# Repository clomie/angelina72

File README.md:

# Angelina72

72/68/64 keys irregular row staggered split keyboard.

## Layout and Default Keymap

# Photos

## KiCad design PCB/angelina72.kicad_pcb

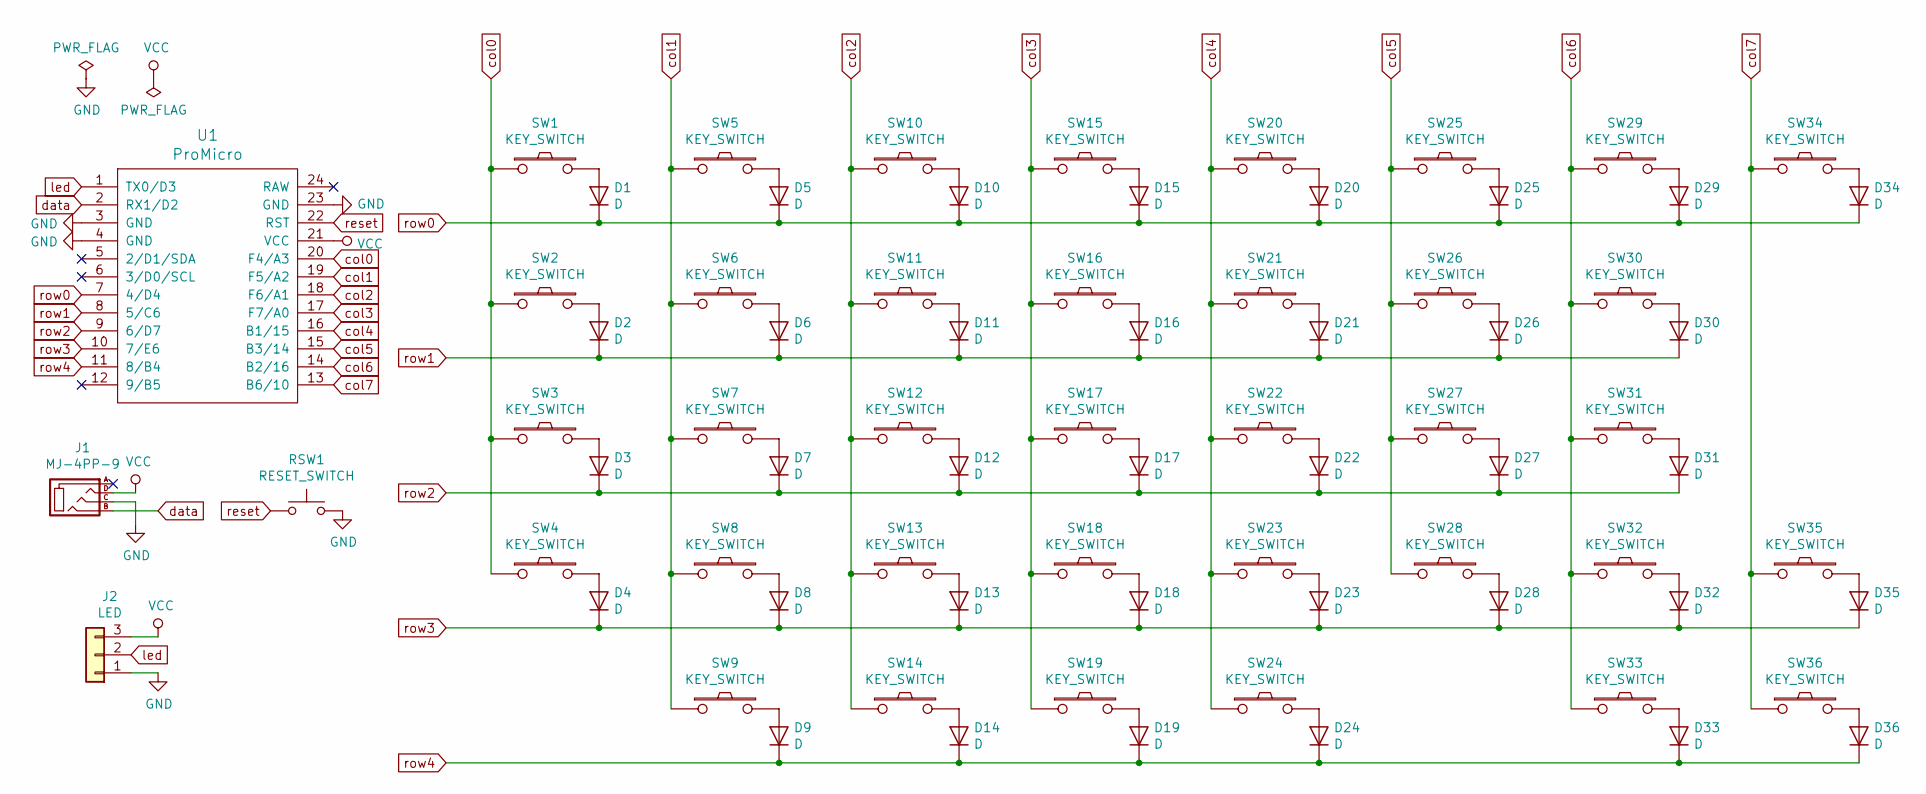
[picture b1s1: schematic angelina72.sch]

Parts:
D1, D2, D3, D4, D5, D6, D7, D8, D9, D10, D11, D12, D13, D14, D15, D16, D17, D18, D19, D20, D21, D22, D23, D24, D25, D26, D27, D28, D29, D30, D31, D32, D33, D34, D35, D36: D; D3_SMD
J1: MJ-4PP-9
J2: LED; StripLED_PAD
RSW1: RESET_SWITCH; ResetSW
SW1, SW2, SW3, SW4, SW5, SW6, SW7, SW8, SW10, SW11, SW12, SW13, SW14, SW15, SW16, SW17, SW18, SW20, SW21, SW22, SW23, SW25, SW26, SW27, SW28, SW29, SW30, SW31, SW32, SW33, SW34, SW35, SW36: KEY_SWITCH; CherryMX_Hotswap_1u
SW9, SW19, SW24: KEY_SWITCH; CherryMX_Hotswap_1.25u
U1: ProMicro

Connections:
GND: J1.C, J2.1, RSW1.2, U1.3 (GND), U1.4 (GND), U1.23 (GND)
unnamed: D1.2 (A), SW1.2
unnamed: D2.2 (A), SW2.2
unnamed: D3.2 (A), SW3.2
unnamed: D4.2 (A), SW4.2
unnamed: D5.2 (A), SW5.2
unnamed: D6.2 (A), SW6.2
unnamed: D7.2 (A), SW7.2
unnamed: D8.2 (A), SW8.2
unnamed: D9.2 (A), SW9.2
unnamed: D10.2 (A), SW10.2
unnamed: D11.2 (A), SW11.2
unnamed: D12.2 (A), SW12.2
unnamed: D13.2 (A), SW13.2
unnamed: D14.2 (A), SW14.2
unnamed: D15.2 (A), SW15.2
unnamed: D16.2 (A), SW16.2
unnamed: D17.2 (A), SW17.2
unnamed: D18.2 (A), SW18.2
unnamed: D19.2 (A), SW19.2
unnamed: D20.2 (A), SW20.2
unnamed: D21.2 (A), SW21.2
unnamed: D22.2 (A), SW22.2
unnamed: D23.2 (A), SW23.2
unnamed: D24.2 (A), SW24.2
unnamed: D25.2 (A), SW25.2
unnamed: D26.2 (A), SW26.2
unnamed: D27.2 (A), SW27.2
unnamed: D28.2 (A), SW28.2
unnamed: D29.2 (A), SW29.2
unnamed: D30.2 (A), SW30.2
unnamed: D31.2 (A), SW31.2
unnamed: D32.2 (A), SW32.2
unnamed: D33.2 (A), SW33.2
unnamed: D34.2 (A), SW34.2
unnamed: D35.2 (A), SW35.2
unnamed: D36.2 (A), SW36.2
VCC: J1.D, J2.3, U1.21 (VCC)
col0: SW1.1, SW2.1, SW3.1, SW4.1, U1.20 (F4/A3)
col1: SW5.1, SW6.1, SW7.1, SW8.1, SW9.1, U1.19 (F5/A2)
col2: SW10.1, SW11.1, SW12.1, SW13.1, SW14.1, U1.18 (F6/A1)
col3: SW15.1, SW16.1, SW17.1, SW18.1, SW19.1, U1.17 (F7/A0)
col4: SW20.1, SW21.1, SW22.1, SW23.1, SW24.1, U1.16 (B1/15)
col5: SW25.1, SW26.1, SW27.1, SW28.1, U1.15 (B3/14)
col6: SW29.1, SW30.1, SW31.1, SW32.1, SW33.1, U1.14 (B2/16)
col7: SW34.1, SW35.1, SW36.1, U1.13 (B6/10)
data: J1.B, U1.2 (RX1/D2)
led: J2.2, U1.1 (TX0/D3)
reset: RSW1.1, U1.22 (RST)
row0: D1.1 (K), D5.1 (K), D10.1 (K), D15.1 (K), D20.1 (K), D25.1 (K), D29.1 (K), D34.1 (K), U1.7 (4/D4)
row1: D2.1 (K), D6.1 (K), D11.1 (K), D16.1 (K), D21.1 (K), D26.1 (K), D30.1 (K), U1.8 (5/C6)
row2: D3.1 (K), D7.1 (K), D12.1 (K), D17.1 (K), D22.1 (K), D27.1 (K), D31.1 (K), U1.9 (6/D7)
row3: D4.1 (K), D8.1 (K), D13.1 (K), D18.1 (K), D23.1 (K), D28.1 (K), D32.1 (K), D35.1 (K), U1.10 (7/E6)
row4: D9.1 (K), D14.1 (K), D19.1 (K), D24.1 (K), D33.1 (K), D36.1 (K), U1.11 (8/B4)

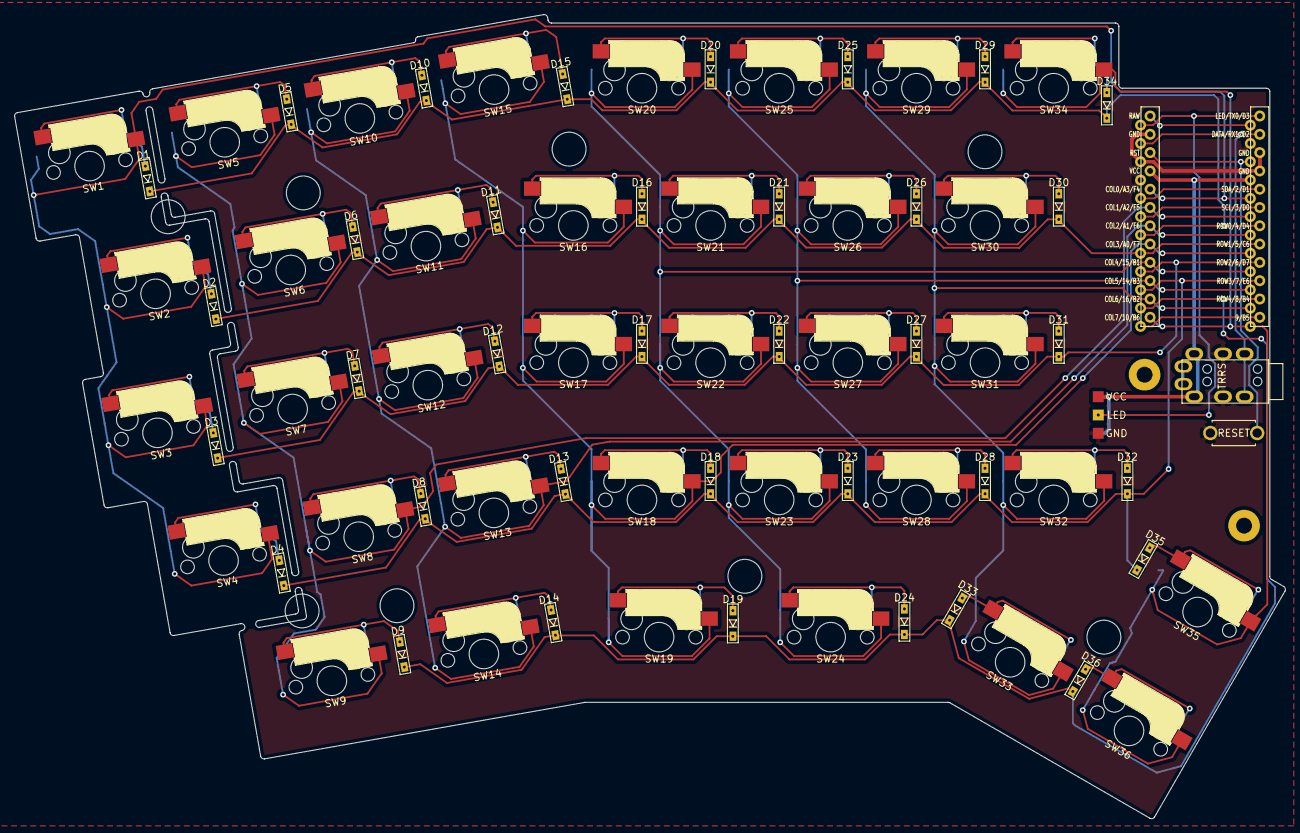
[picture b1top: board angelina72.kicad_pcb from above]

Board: 2 copper layers, 176.4 x 111.6 mm, 76 parts (0 on the bottom side), 54 nets.

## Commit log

2019-08-24 Add readme
2019-09-08 Added PCB bottom plate
2019-10-19 Add layout
2019-10-26 Added PCB and top plate
2019-10-26 Update PCB, top plate
2019-10-26 Add bottom plate
2019-10-28 Fix PCB, top plate, bottom plate
2019-10-31 Update PCBs
2019-11-02 Add acrylic plate
2019-11-02 Cleanup
2019-11-05 Update acrylic case
2019-11-05 Add wiring.svg
2019-11-12 Add build guide
2019-11-14 Add firmware
2019-11-16 Update buildguide
2019-11-16 Add buildguide
2019-12-28 アクリル積層ケースの再設計(左手)
2020-01-13 左手用のアクリル積層ケースを追加
2020-01-13 ちょっと修正
2020-01-13 右手用のアクリル積層ケースを追加
2020-01-16 積層アクリル用svg追加
2020-01-16 フォルダ整理
2020-01-21 PCBの空きレイヤーでscad用のポリゴンを書いた
2020-01-21 kicadポリゴンから頂点を抽出するスクリプトを書いた
2020-01-26 アクリルサンドイッチケース追加
